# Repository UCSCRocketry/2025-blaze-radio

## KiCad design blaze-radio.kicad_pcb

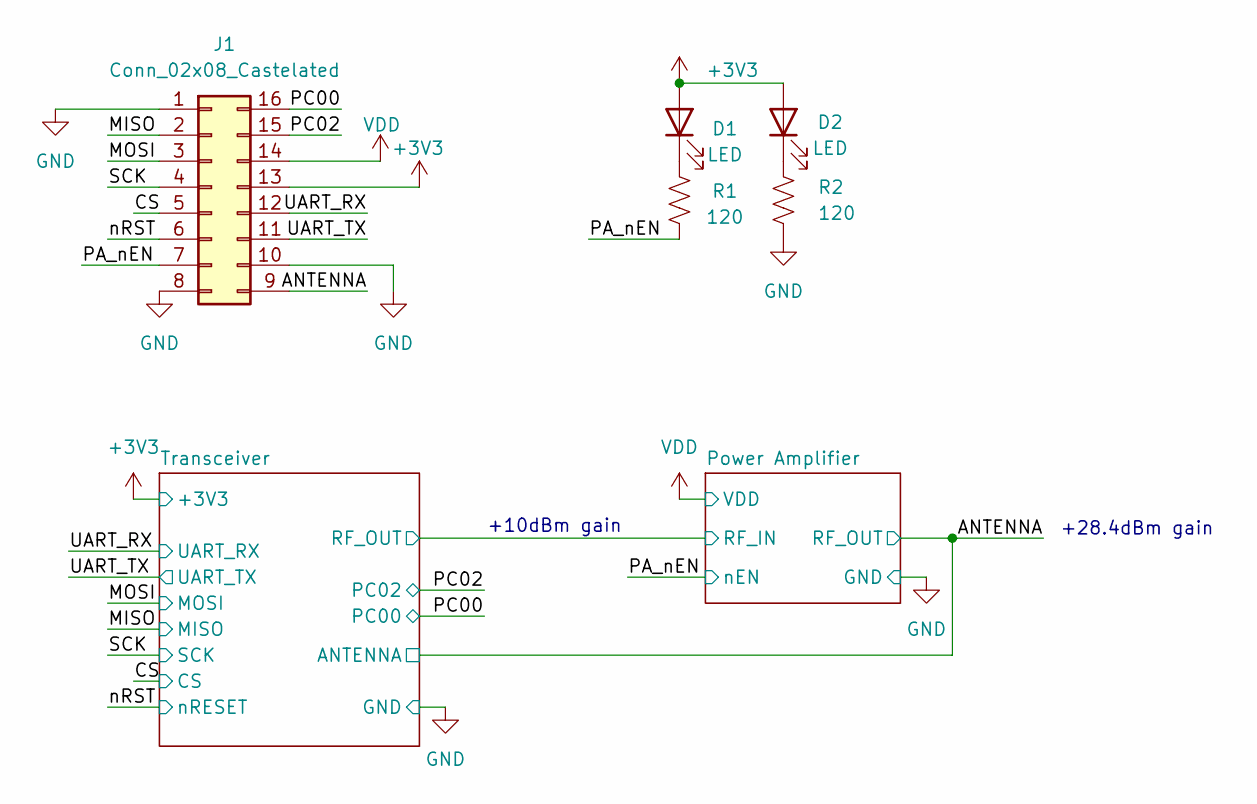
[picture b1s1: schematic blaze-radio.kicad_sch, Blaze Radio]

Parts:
D1, D2: LED; LED_0201_0603Metric
J1: Conn_02x08_Castelated; RFMxx
R1, R2: 120; R_0201_0603Metric

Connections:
+3V3: D1.2 (A), D2.2 (A), J1.13; also elsewhere on the board
/ANTENNA: J1.9; also elsewhere on the board
/CS: J1.5; also elsewhere on the board
/MISO: J1.2; also elsewhere on the board
/MOSI: J1.3; also elsewhere on the board
/PA_nEN: J1.7, R1.2; also elsewhere on the board
/PC00: J1.16; also elsewhere on the board
/PC02: J1.15; also elsewhere on the board
/SCK: J1.4; also elsewhere on the board
/UART_RX: J1.12; also elsewhere on the board
/UART_TX: J1.11; also elsewhere on the board
/nRST: J1.6; also elsewhere on the board
GND: J1.1, J1.8, J1.10, R2.2; also elsewhere on the board
unnamed: D1.1 (K), R1.1
unnamed: D2.1 (K), R2.1
VDD: J1.14; also elsewhere on the board

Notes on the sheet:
+28.4dBm gain
+10dBm gain

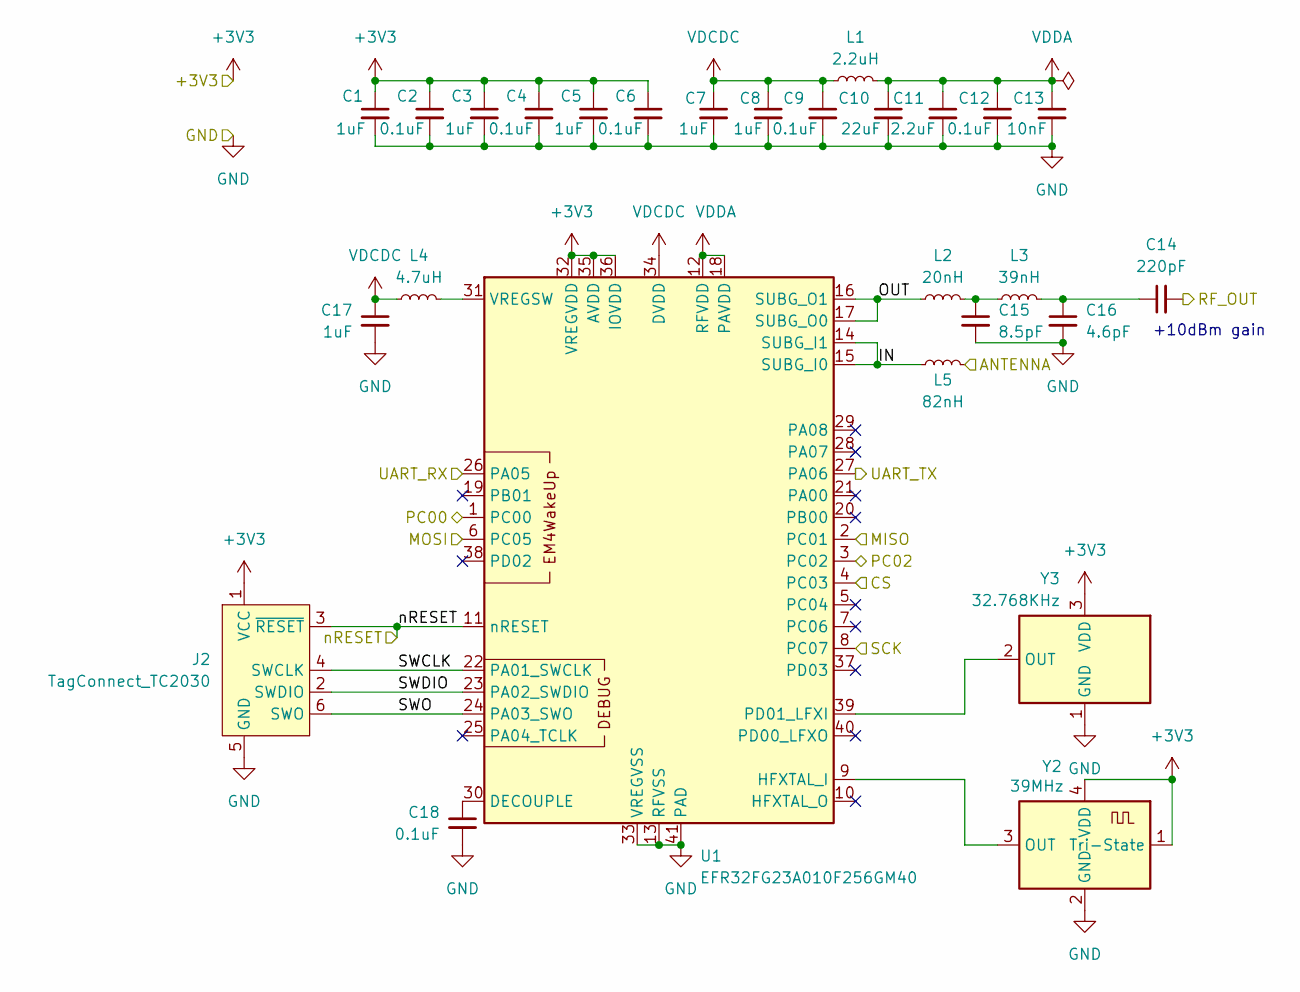
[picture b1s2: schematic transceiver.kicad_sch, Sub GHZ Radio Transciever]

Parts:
C1, C3, C5, C7, C8, C17: 1uF; C_0201_0603Metric
C2, C4, C6, C9, C12, C18: 0.1uF; C_0201_0603Metric; Part_Number GRM155R71C104KA88D
C10: 22uF; C_0402_1005Metric
C11: 2.2uF; C_0402_1005Metric; Part_Number GRM188C71E225KE11D
C13: 10nF; C_0201_0603Metric; Part_Number GRM1555C1H102JA01D
C14: 220pF; C_0402_1005Metric
C15: 8.5pF; C_0201_0603Metric
C16: 4.6pF; C_0201_0603Metric
J2: TagConnect_TC2030; Tag-Connect_TC2030-IDC-NL_2x03_P1.27mm_Vertical
L1: 2.2uH; L_0402_1005Metric
L2: 20nH; L_0402_1005Metric
L3: 39nH; L_0402_1005Metric
L4: 4.7uH; L_0603_1608Metric
L5: 82nH; L_0402_1005Metric
U1: EFR32FG23A010F256GM40; QFN-40-1EP_5x5mm_P0.4mm_EP3.6x3.6mm
Y2: 39MHz; Crystal_SMD_2016-4Pin_2.0x1.6mm
Y3: 32.768KHz; OSC_SIT1532AI-J4-DCC-32.768D; LCSC C367054

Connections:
+3V3: C1.1, C2.1, C3.1, C4.1, C5.1, C6.1, J2.1 (VCC), U1.32 (VREGVDD), U1.35 (AVDD), U1.36 (IOVDD), Y2.1 (Tri-State), Y2.4 (VDD), Y3.3 (VDD); also elsewhere on the board
/ANTENNA: L5.2; also elsewhere on the board
/CS: U1.4 (PC03); also elsewhere on the board
/MISO: U1.2 (PC01); also elsewhere on the board
/MOSI: U1.6 (PC05); also elsewhere on the board
/PC00: U1.1 (PC00); also elsewhere on the board
/PC02: U1.3 (PC02); also elsewhere on the board
/Power Amplifier/RF_IN: C14.2; also elsewhere on the board
/SCK: U1.8 (PC07); also elsewhere on the board
/Transceiver/IN: L5.1, U1.14 (SUBG_I1), U1.15 (SUBG_I0)
/Transceiver/OUT: L2.1, U1.16 (SUBG_O1), U1.17 (SUBG_O0)
/Transceiver/SWCLK: J2.4 (SWCLK), U1.22 (PA01_SWCLK)
/Transceiver/SWDIO: J2.2 (SWDIO), U1.23 (PA02_SWDIO)
/Transceiver/SWO: J2.6 (SWO), U1.24 (PA03_SWO)
/UART_RX: U1.26 (PA05); also elsewhere on the board
/UART_TX: U1.27 (PA06); also elsewhere on the board
/nRST: J2.3 (~RESET), U1.11 (nRESET); also elsewhere on the board
GND: C1.2, C2.2, C3.2, C4.2, C5.2, C6.2, C7.2, C8.2, C9.2, C10.2, C11.2, C12.2, C13.2, C15.2, C16.2, C17.2, C18.2, J2.5 (GND), U1.13 (RFVSS), U1.33 (VREGVSS), U1.41 (PAD), Y2.2 (GND), Y3.1 (GND), Y3.4 (GND); also elsewhere on the board
unnamed: C14.1, C16.1, L3.2
unnamed: C15.1, L2.2, L3.1
unnamed: C18.1, U1.30 (DECOUPLE)
unnamed: U1.9 (HFXTAL_I), Y2.3 (OUT)
unnamed: U1.39 (PD01_LFXI), Y3.2 (OUT)
unnamed: L4.2, U1.31 (VREGSW)
VDCDC: C7.1, C8.1, C9.1, C17.1, L1.1, L4.1, U1.34 (DVDD)
VDDA: C10.1, C11.1, C12.1, C13.1, L1.2, U1.12 (RFVDD), U1.18 (PAVDD)

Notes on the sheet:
+10dBm gain

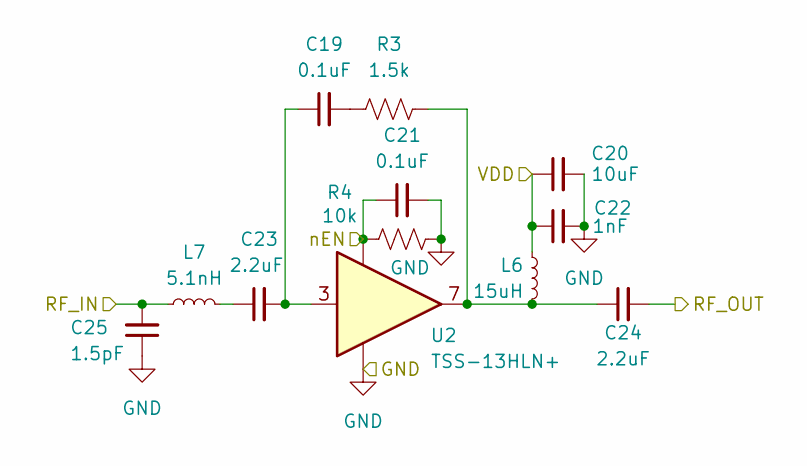
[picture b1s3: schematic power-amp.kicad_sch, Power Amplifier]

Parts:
C19, C21: 0.1uF; C_0201_0603Metric; Part_Number GRM155R71C104KA88D
C20: 10uF; C_0402_1005Metric; Part_Number GRM21BC71E106KE11L
C22: 1nF; C_0201_0603Metric
C23, C24: 2.2uF; C_0402_1005Metric; Part_Number GRM188C71E225KE11D
C25: 1.5pF; C_0201_0603Metric; Part_Number GRM1555C1H1R5CA1D
L6: 15uH; L_0805_2012Metric_Pad1.05x1.20mm_HandSolder; Part_Number LQH32DN150K53L
L7: 5.1nH; L_0402_1005Metric; Part_Number 0603CS-5N1XJLU
R3: 1.5k; R_0201_0603Metric
R4: 10k; R_0201_0603Metric
U2: TSS-13HLN+; QFN-12-1EP_3x3mm_P0.5mm_EP1.45x1.45mm

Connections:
/ANTENNA: C24.2; also elsewhere on the board
/PA_nEN: C21.1, R4.1, U2.1 (VG); also elsewhere on the board
/Power Amplifier/RF_IN: C25.2, L7.1; also elsewhere on the board
GND: C20.2, C21.2, C22.2, C25.1, R4.2, U2.2 (NC), U2.4 (NC), U2.5 (NC), U2.6 (NC), U2.8 (NC), U2.9 (NC), U2.10 (NC), U2.11 (NC), U2.12 (NC), U2.PAD (GND); also elsewhere on the board
unnamed: C19.2, R3.1
unnamed: C23.1, L7.2
unnamed: C19.1, C23.2, U2.3 (IN)
unnamed: C24.1, L6.2, R3.2, U2.7 (OUT)
VDD: C20.1, C22.1, L6.1; also elsewhere on the board

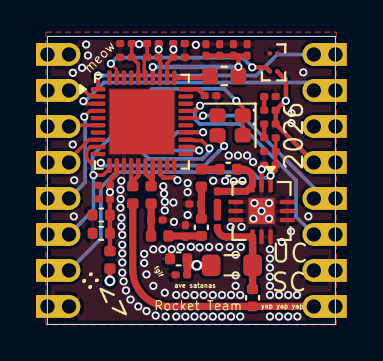
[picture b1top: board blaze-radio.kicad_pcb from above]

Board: 4 copper layers, 16.0 x 16.0 mm, 44 parts (1 on the bottom side), 34 nets.

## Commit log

2026-01-29 Radio design
2026-01-30 Added git ignore
2026-01-31 Readability updates
2026-03-19 Routing updates
